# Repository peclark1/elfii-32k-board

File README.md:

# Netronics ELF II — Standalone 32 KiB SRAM Expansion Card

A period-styled, through-hole 32 KiB SRAM card for the **original Netronics
ELF II / RCA CDP1802 expansion bus**, designed to use the full-size historical
86-contact, two-sided expansion-card outline.

**Engineering status: active Hyperboard-derived redesign. No fabrication
authorization; do not insert the PCB into a working ELF II yet.**

## Current electrical design

The first-generation custom 74HCT273/XOR/OR implementation is **superseded**.
The active schematic follows the AVI ELF II Hyperboard Rev 2 RAM circuit:

- **U1 74HC573:** transparently captures multiplexed high address A8–A15
  during TPA; direct MA0–MA7 become the low byte A0–A7.
- **U2 CY62256-compatible 32K × 8 SRAM:** direct D0–D7, /MRD to /OE,
  /MWR to /WE, and decoded active-low /CS.
- **U3 74HC151:** selects which of eight 4 KiB pages are enabled by SW1,
  with RN1 providing 22 kΩ pull-downs. The HC151 is an intentional
  pin-compatible reliability adaptation of the original Hyperboard LS151
  (documented TTL LOW-current concern).
- **U4 CD4011:** derives complementary A15 for a simple selectable
  LOW $0000–$7FFF versus HIGH $8000–$FFFF memory half.
- Local decoupling, a bulk capacitor and an optional *normally open*
  early-Netronics motherboard-RAM-disable feature.

The 86 edge pads and original measured card outline are **not being
redesigned**. The new circuit omits the Hyperboard's ROM, UART, I/O,
cassette and boot functions.

## KiCad schematic and PCB status

- `hardware/kicad/elfii-32k-board.kicad_sch` is the **active new
  Hyperboard-derived schematic**. KiCad 9 ERC and pin-specific netlist
  regression tests have passed (138 checked pin memberships across 41 nets).
- `hardware/kicad/elfii-32k-board.kicad_pcb` is synchronized with the active electrical schematic on the **dedicated review branch**. `main` continues to retain its older A5 PCB study until final release gates are met.
- `scripts/build_pcb_candidate.py` creates a physically preserved,
  new-architecture through-hole PCB from the current KiCad netlist,
  without touching the obsolete PCB traces. The initial candidate has
  14 footprints and begins unrouted.
- `.github/workflows/hyperboard-routing-trial.yml` runs an isolated
  Freerouting trial on the new candidate, then checks a separate routed
  PCB using native KiCad 9 DRC and uploads reviewable results as a GitHub
  Actions artifact. Routing results are **experimental**, not yet promoted
  to the authoritative PCB.

The `SCHEMATIC_REBUILD_IN_PROGRESS` marker keeps outdated PCB
consistency/DRC checks from mistakenly accepting the old file as current.
It is removed only after a genuine schematic-to-PCB synchronization.

## Verified routing milestone — 12 October 2026

The initial 426-track/27-via trial was superseded by the coordinator-accepted [revised 438-track, 35-via Hyperboard PCB preview](https://github.com/peclark1/elfii-32k-board/tree/experiment/hyperboard-route-b57bb49a), where **J1-69 is physically routed to JP2-1**. The [pre-fabrication review branch](https://github.com/peclark1/elfii-32k-board/tree/feature/hyperboard-pcb-prefab-review) adds two GND zones, moves a dangerous +5V via out of the finger region, and independently verifies the copper in CI. This is a **review only, not fabrication authorization**. See [the updated PCB review](docs/design/prefabrication-layout-review-2026-10-12.md), [measured +5V and decoupling paths](docs/design/prefab-power-and-decoupling-measurements-2026-10-12.md), and [the historical checkpoint](docs/design/hyperboard-routing-checkpoint-2026-10-12.md).

## Critical safety holds

1. **J1-69:** original Slot-5 motherboard-RAM-disable behavior is established prior project evidence. The revised PCB connects J1-69 to JP2-1 and JP2-2 to GND; **shunt is normally open**, with no permanent ground strap. **J1-82 remains NC** until independently understood.
2. Verify collisions and memory mapping against onboard 2101 RAM,
   Giant Board and any other memory devices.
3. Check 1802 TPA/address, /CS, /OE and /WE timing and bus contention on
   actual hardware.
4. Resolve intentional edge-finger DRC clearances with the fabricator's
   gold fingers, plating, bevel, PCB thickness and mating-socket specs.
5. Require full electrically matching PCB netlist, fully routed copper,
   no unexplained ERC/DRC issues, and physical/visual review prior to Gerbers.

## Reference and design documentation

- [Hyperboard RAM source trace](docs/design/hyperboard-ram-circuit-trace.md)
- [New electrical architecture](docs/design/hyperboard-ram-rebuild.md)
- [74LS151 input-margin review](docs/design/page-select-ttl-input-margin.md)
- [Early ELF II bus bench verification](docs/design/early-elfii-bus-bench-validation.md)
- [Card-edge CAM and fabrication hold](docs/design/card-edge-cam-manufacturing-review-2026-10-12.md)
- [Power feed and bypass copper measurements](docs/design/prefab-power-and-decoupling-measurements-2026-10-12.md)
- [KiCad project instructions](hardware/kicad/README.md)
- [Original ELF II period sources](docs/reference/source-notes.md)

## License

License selection pending. Original Netronics and AVI/Hyperboard drawings
are historical reference material, not presumed freely redistributable.

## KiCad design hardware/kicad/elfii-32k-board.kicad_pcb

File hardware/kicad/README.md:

# ELF II 32K SRAM KiCad — Hyperboard-derived review

**Review branch only:** `feature/hyperboard-pcb-prefab-review`.
**Do not fabricate, install, or replace main's authoritative PCB.**

The schematic follows the AVI Hyperboard Rev 2 RAM path (U1 74HC573,
U2 CY62256, U3 74HC151, U4 CD4011). The source PCB on this feature
branch is the **physically routed Hyperboard-derived revision**, not
the obsolete A5 netlist and routing study still preserved on main.

The `SCHEMATIC_REBUILD_IN_PROGRESS` marker intentionally remains.
The dedicated `prefabrication-review.yml` workflow **always** checks
the fully routed preview, regardless of this marker, using original
mechanical regression, source netlist/ERC, netlist-to-PCB pad matching,
insertion-area via screening, full copper connectivity and filled
native KiCad 9 DRC in the actual local footprint-library directory.

The accepted revision connects J1-69 to JP2-1; JP2-2 goes to GND.
Closing the removable shunt invokes the **previously established
Slot-5 motherboard-RAM-disable** function. The shunt is normally open.
J1-82 remains unconnected pending independent verification.

The physical review adds two GND zones kept behind the edge-finger
tongue and moves a +5V via out of the bevel/finger region. Long narrow
power routing and copper neckdowns, decoupling loops, physical
connector height/fit, ground-zone effectiveness, early-ELF timing,
memory coexistence and manufacturer-approved hard-gold/edge bevel
remain open.

See `docs/design/prefabrication-layout-review-2026-10-12.md` for
measured routing facts and release holds.

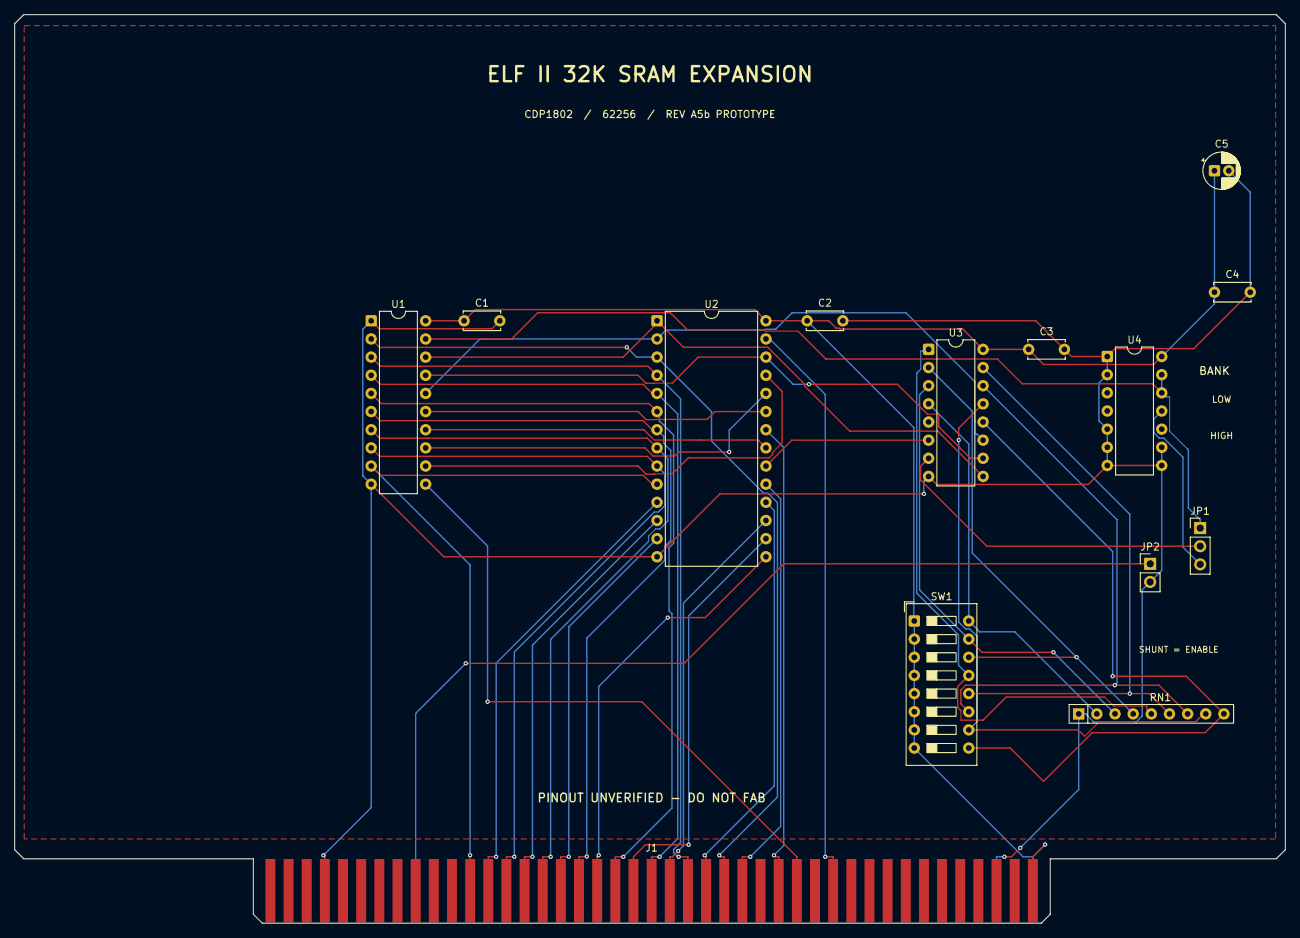
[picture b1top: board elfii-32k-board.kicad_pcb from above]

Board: 2 copper layers, 177.8 x 127.1 mm, 14 parts (0 on the bottom side), 41 nets.

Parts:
C1, C2, C3, C4: 100n; C_Disc_D5.0mm_W2.5mm_P5.00mm
C5: 10u POLARIZED PIN1=+5V; CP_Radial_D5.0mm_P2.00mm
J1: ELFII_86_MECH_UNVERIFIED; ELFII_Edge_86_Rev2_Unverified
JP1: RAM_HALF; PinHeader_1x03_P2.54mm_Vertical
JP2: MB_RAM_DISABLE_SLOT5; PinHeader_1x02_P2.54mm_Vertical
RN1: 8x22K; R_Array_SIP9
SW1: RAM_PAGE_ENABLE; SW_DIP_SPSTx08_Slide_9.78x22.5mm_W7.62mm_P2.54mm
U1: 74HC573; DIP-20_W7.62mm
U2: CY62256-70PC; DIP-28_W15.24mm
U3: 74HC151; DIP-16_W7.62mm
U4: CD4011; DIP-14_W7.62mm

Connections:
+5V: C1.1, C2.1, C3.1, C4.1, C5.1, J1.1, J1.2, SW1.1, SW1.2, SW1.3, SW1.4, SW1.5, SW1.6, SW1.7, SW1.8, U1.20, U2.28, U3.16, U4.14
/A8: U1.12, U2.25
/A9: U1.13, U2.24
/A10: U1.14, U2.21
/A11: U1.15, U2.23
/A12: U1.16, U2.2, U3.11
/A13: U1.17, U2.26, U3.10
/A14: U1.18, U2.1, U3.9
/A15: JP1.1, U1.19, U4.12, U4.13
/A15_N: JP1.3, U4.11
/D0: J1.62, U2.11
/D1: J1.58, U2.12
/D2: J1.54, U2.13
/D3: J1.50, U2.15
/D4: J1.46, U2.16
/D5: J1.42, U2.17
/D6: J1.38, U2.18
/D7: J1.34, U2.19
/HALF_EN: JP1.2, U3.7
/MA0: J1.64, U1.9, U2.10
/MA1: J1.60, U1.8, U2.9
/MA2: J1.56, U1.7, U2.8
/MA3: J1.52, U1.6, U2.7
/MA4: J1.48, U1.5, U2.6
/MA5: J1.44, U1.4, U2.5
/MA6: J1.40, U1.3, U2.4
/MA7: J1.36, U1.2, U2.3
/MB_RAM_DISABLE: J1.69, JP2.1
/PAGE0: RN1.2, SW1.16, U3.4
/PAGE1: RN1.3, SW1.15, U3.3
/PAGE2: RN1.4, SW1.14, U3.2
/PAGE3: RN1.5, SW1.13, U3.1
/PAGE4: RN1.6, SW1.12, U3.15
/PAGE5: RN1.7, SW1.11, U3.14
/PAGE6: RN1.8, SW1.10, U3.13
/PAGE7: RN1.9, SW1.9, U3.12
/RAM_CS_N: U2.20, U3.6
/TPA: J1.28, U1.11
/~MRD: J1.30, U2.22
/~MWR: J1.24, U2.27
GND: C1.2, C2.2, C3.2, C4.2, C5.2, J1.5, J1.80, JP2.2, RN1.1, U1.1, U1.10, U2.14, U3.8, U4.1, U4.2, U4.5, U4.6, U4.7, U4.8, U4.9

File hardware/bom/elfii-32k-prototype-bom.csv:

Reference,Quantity,Value,Footprint,Recommended specification,Fitment and ordering notes
U1,1,74HC573,Package_DIP:DIP-20_W7.62mm,5 V 74HC573 octal transparent latch PDIP-20,Socket recommended; Hyperboard high-address capture
U2,1,CY62256-70PC,Package_DIP:DIP-28_W15.24mm,32K x 8 5 V SRAM DIP-28 70 ns or verified compatible,Check real replacement pinout and 5 V rating; socket
U3,1,74HC151,Package_DIP:DIP-16_W7.62mm,5 V 74HC151 multiplexer PDIP-16,Do NOT substitute 74LS151 with 22k pulldowns
U4,1,CD4011,Package_DIP:DIP-14_W7.62mm,5 V CD4011 quad NAND PDIP-14,One gate provides inverted A15; spare inputs defined
SW1,1,RAM_PAGE_ENABLE,Button_Switch_THT:SW_DIP_SPSTx08_Slide_9.78x22.5mm_W7.62mm_P2.54mm,8 position SPST DIP slide switch 2.54 mm pitch,Check actual chosen vendor footprint before buying
RN1,1,8x22K PULLDOWN,Resistor_THT:R_Array_SIP9,9 pin bussed resistor network 8 x 22k 5 percent,SINGLE common to GND; not eight isolated resistors
JP1,1,RAM_HALF LOW/HIGH,Connector_PinHeader_2.54mm:PinHeader_1x03_P2.54mm_Vertical,1x3 2.54 mm breakaway male pin header,Include one removable shorting shunt for LOW or HIGH
JP2,1,MB_RAM_DISABLE,Connector_PinHeader_2.54mm:PinHeader_1x02_P2.54mm_Vertical,1x2 2.54 mm male pin header,Do NOT fit shunt by default; optional RAM-disable to GND
C1-C4,4,100n,Capacitor_THT:C_Disc_D5.0mm_W2.5mm_P5.00mm,100 nF ceramic >=16 V radial 5 mm pitch,Local 100 nF for each U1-U4
C5,1,10u,Capacitor_THT:CP_Radial_D5.0mm_P2.00mm,10 uF electrolytic >=10 V 5 mm body 2 mm pin pitch,Observe polarity; physical height/diameter check
J1,1,ELFII_P3_86,ELFII_Expansion:ELFII_Edge_86_Rev2_Unverified,86 plated on-board gold-finger contacts,INTEGRAL PCB not a separately purchasable connector
PCB,1,ELFII_32K_BOARD,Custom 177.8x127.127mm two-layer FR4,1.6mm nominal 1oz outer copper selective hard gold requested,NOT FOR ORDER until CAM/process release
